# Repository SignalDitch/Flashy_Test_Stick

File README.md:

# Flashy_Test_Stick
Reflow test for popular Addressable LED packages

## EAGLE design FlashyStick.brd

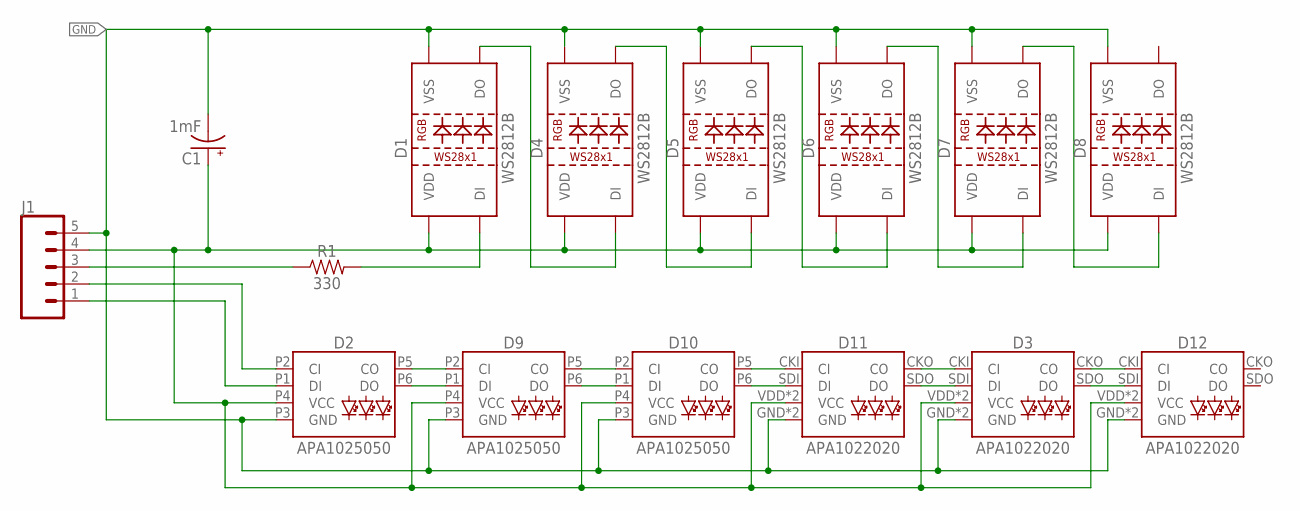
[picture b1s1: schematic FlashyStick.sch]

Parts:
C1: 1mF; CPOL-RADIAL-5MM-10MM
D1, D4, D5, D6, D7, D8: WS2812B
D2, D9, D10: APA1025050; APA102-5050
D3, D11, D12: APA1022020; APA102-2020
J1: CONN_05; 1X05
R1: 330; 0603

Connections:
GND: C1.-, D1.3 (VSS), D2.P3 (GND), D3.GND, D3.GNDPAD (GND), D4.3 (VSS), D5.3 (VSS), D6.3 (VSS), D7.3 (VSS), D8.3 (VSS), D9.P3 (GND), D10.P3 (GND), D11.GND, D11.GNDPAD (GND), D12.GND, D12.GNDPAD (GND), J1.5
unnamed: J1.3, R1.1
unnamed: D1.4 (DI), R1.2
unnamed: D1.2 (DO), D4.4 (DI)
unnamed: D4.2 (DO), D5.4 (DI)
unnamed: D5.2 (DO), D6.4 (DI)
unnamed: D6.2 (DO), D7.4 (DI)
unnamed: D7.2 (DO), D8.4 (DI)
unnamed: D2.P2 (CI), J1.2
unnamed: D2.P1 (DI), J1.1
unnamed: D2.P5 (CO), D9.P2 (CI)
unnamed: D2.P6 (DO), D9.P1 (DI)
unnamed: D9.P5 (CO), D10.P2 (CI)
unnamed: D9.P6 (DO), D10.P1 (DI)
unnamed: D10.P5 (CO), D11.CKI (CI)
unnamed: D10.P6 (DO), D11.SDI (DI)
unnamed: D3.CKI (CI), D11.CKO (CO)
unnamed: D3.SDI (DI), D11.SDO (DO)
unnamed: D3.CKO (CO), D12.CKI (CI)
unnamed: D3.SDO (DO), D12.SDI (DI)
unnamed: C1.+, D1.1 (VDD), D2.P4 (VCC), D3.VDD (VCC), D3.VDDPAD (VCC), D4.1 (VDD), D5.1 (VDD), D6.1 (VDD), D7.1 (VDD), D8.1 (VDD), D9.P4 (VCC), D10.P4 (VCC), D11.VDD (VCC), D11.VDDPAD (VCC), D12.VDD (VCC), D12.VDDPAD (VCC), J1.4

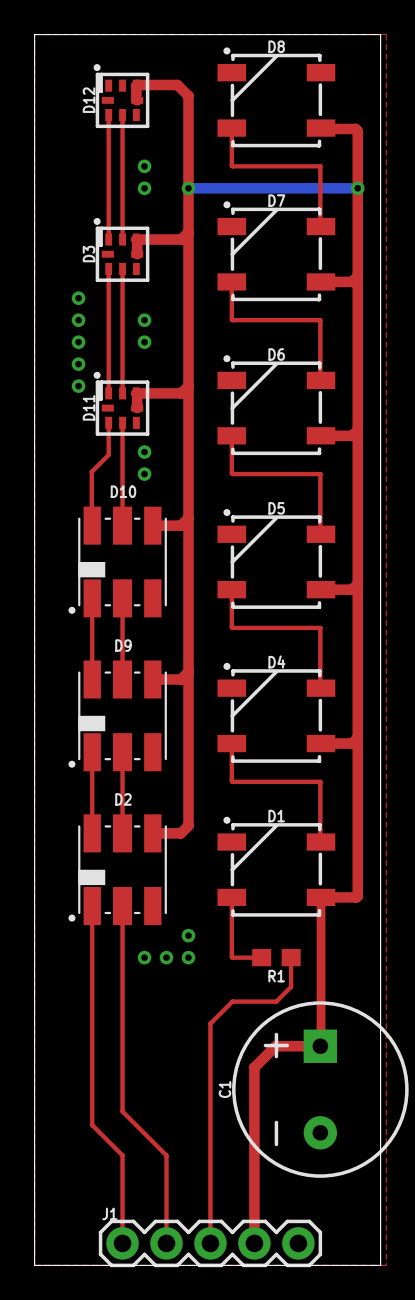
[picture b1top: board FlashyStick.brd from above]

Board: 2 copper layers, 20.0 x 71.1 mm, 15 parts (0 on the bottom side), 21 nets.

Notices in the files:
parts and their libraries:
SparkFun-Capacitors: Licensing: Creative Commons ShareAlike 4.0 International - https://creativecommons.org/licenses/by-sa/4.0
